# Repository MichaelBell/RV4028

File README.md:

# RV4028 - A hackable Risc-V computer

RV4028 is intended to be a modular Risc-V computer, similar to the excellent [RC2014 Z80](https://rc2014.co.uk/) homebrew computer.

The idea is to create a minimal Risc-V system that is easy to understand and extend.

The inspiration for this came from [@theJPster](https://github.com/thejpster)'s [post](https://bsky.app/profile/thejpster.org.uk/post/3m3ngtx5sfc2i).

All hardware and software are open source and permissively licensed.

## Architecture

The system bus has a 32-bit address and 16-bit data, which fits reasonably well with an RV32 system and readily available (P)SRAM chips, and runs at 3.3V.

Modules are attached by an 80-pin dual row header, similar to RC2014 modules but with 2 rows of pins instead of 1.  2mm pitch headers are used instead of 2.54mm, this makes boards slightly smaller (and cheaper), and also avoids the possibility of boards being plugged into RC2014 by mistake.

However, the pinout is chosen such that RC2014 modules might be compatible, if 3v3 capable components are used and a backplane with additional 2.54mm pitch sockets were created.  The pinout is also chosen such that modules not requiring access to the full bus can use just a single row.

## Software

The intention is to be able to run standard RV32I programs with a C SDK.  A Micropython port and Rust support are likely.

It is currently not a goal to support either real time operating systems (although this may be possible in future), or Linux (which would likely not be possible without moving to a larger FPGA).

# Initial modules

## CPU

Keeping things minimal and simple, we use a Bruno Levy's [FemtoRV](https://github.com/BrunoLevy/learn-fpga/tree/master/FemtoRV) Quark (RV32I) core with some small modifications, and a wrapper to handle breaking each 32-bit data access into 16-bit accesses.  This is the most minimal Risc-V instruction set and can fit in a small FPGA, so we use an ICE40 [HX1K](https://www.latticesemi.com/ice40), which is available in a 100-pin QFP.

A small flash is required for the FPGA configuration, a header will be provided that will allow the FPGA to be held in reset and the flash programmed.  Although it is significantly larger than required, using a 1MB [W25Q80DV](https://www.lcsc.com/datasheet/C14086.pdf) seems cost effective. 

[Schematic](cpu/cpu.pdf)

## RAM

The two candidates here are PSRAM, such as the [IS66WVE](https://www.lcsc.com/datasheet/C1350157.pdf), or SRAM such as the [CY7C1041G30](https://www.lcsc.com/datasheet/C2944680.pdf).

The PSRAM is larger but slower, and the larger capacities only seem available in BGA packages.  The linked SRAM is available in TSOP, which may allow for easier assembly.

The current RAM module uses the PSRAM.

[Schematic](ram/ram.pdf)

## ROM

Something like [SST39VF3202C](https://www.lcsc.com/datasheet/C637403.pdf) looks suitable, and available at the same access speed as the PSRAM (70ns).

ROM might not be required - we can embed a small amount of ROM (6kB) in the CPU gateware which could be enough for a simple SD card driver, allowing a program to be loaded from SD card to RAM without any ROM.

## IO

An [RP2350B](https://datasheets.raspberrypi.com/rp2350/rp2350-datasheet.pdf) is used for IO.  The board should include:
- Two UARTs
- Two I2C broken out to Qw/ST compatible ports
- A micro SD card socket
- An SPI with a couple of chip selects (this should be made easy to connect to the CPU for updating the gateware)
- Some GPIO

8 bits of address should easily be sufficient, and 8 bits of data should also be fine, which allows this to be single row.

I'm tempted to put USB on a couple of the spare backplane pins, so a single USB connection can power the system and be used to communicate with/program the RP2350.

If we also wired clock and reset from the RP2350 then it could provide a clock, meaning a separate clock module would not be required.

[Schematic](io/io.pdf) | [More details](io/README.md)

## Clock

As above, a clock module likely won't be required, but it is a nice educational addition, and would allow the machine to be used without the RP2350 based IO module.

A 14.7456MHz crystal would seem appropriate - double the clock rate of the RC2014.  Assuming IS66WVE PSRAM is used, the maximum reliable clock rate of the system should be around 17-18MHz (TBC).

An [SN74LVC1GX04](https://www.lcsc.com/datasheet/C2653063.pdf) could be used to drive the crystal.

## Backplane

USB-C socket, with data wired to spare pins for RP2350 on IO board.

AP2112K for 3.3V supply.  3v3 enable is delayed by a few milliseconds to help with power sequencing on the CPU board (the core power to the FPGA should be applied before IO voltage).

Decoupling caps, LED, reset button.  Use surface mount headers for the 2x40 pin connectors, allows all the signals to run above a nice unbroken ground plane, rather than having loads of through holes breaking up the ground planes.

# Bus timing

Addresses are always 16-bit aligned and a byte mask is used for single byte stores.

All writes complete in a two cycles.  Reads normally complete in two cycles, but wait may be asserted to extend the read cycle.

MREQ is intended to be wired to the (P)SRAM CE, so must be pulsed regularly even if reads are continuous in order to avoid exceeding max CE assertion time on PSRAM.  This is acheived by pulsing it high in the first half clock of each read cycle.  MREQ remains low at the start of a write cycle in order to support a faster clock speed when used with a IS66WVE.

IORQ is not required as the address space is sufficiently large.  It is simply set to ~A31.

LO_ADDR indicates if the address is in the bottom 16MB of the address space, to reduce the amount of address checking logic required on low addressed modules.

## Expected RAM implementation

RAM access is controlled by CE, OE, WE and byte selects.

* Address high bits are compared for the chip, CE is never asserted if the address doesn't match
* CE is MREQ
* WE is WR
* OE is RD
* Byte selects are MSK.

Writes are latched by deasserting WE and CE.  So a full store instruction that read the instruction and wrote data back to the same RAM chip would look like:

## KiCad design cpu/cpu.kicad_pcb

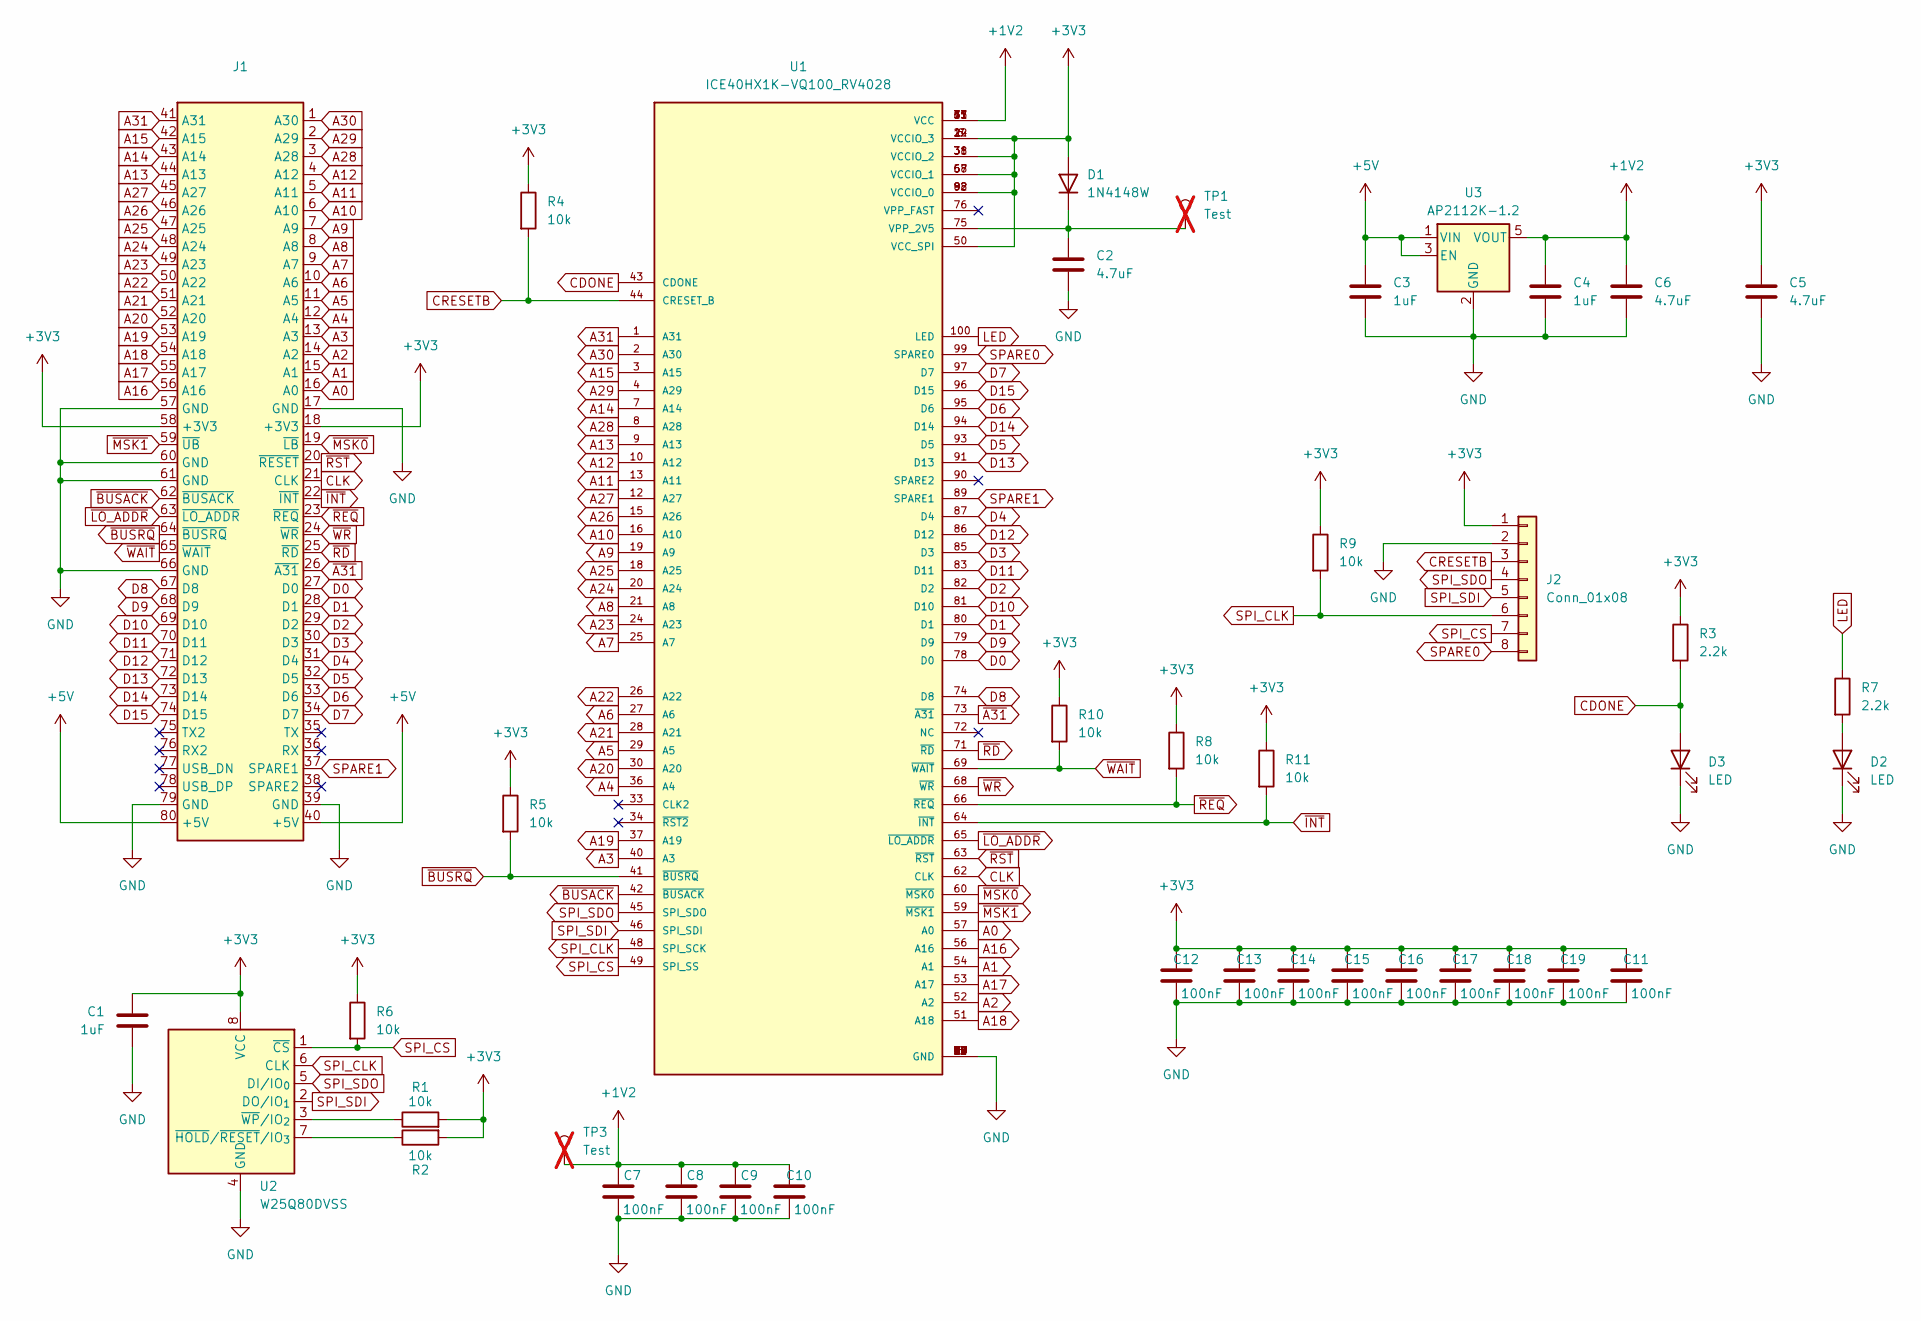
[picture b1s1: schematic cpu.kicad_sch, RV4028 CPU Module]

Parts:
C1, C3, C4: 1uF; C_0603_1608Metric; JLC C15849
C2, C5, C6: 4.7uF; C_0603_1608Metric; JLC C19666
C7, C8, C9, C10, C11, C12, C13, C14, C15, C16, C17, C18, C19: 100nF; C_0402_1005Metric; JLC C1525
D1: 1N4148W; D_SOD-123F; JLC C81598
D2: LED; LED_0603_1608Metric; JLC C2286
D3: LED; LED_0603_1608Metric; JLC C2290
J1: Module_2mm; JLC C3407
J2: Conn_01x08; PinHeader_1x08_P2.54mm_Vertical; JLC C5383116
R1, R2, R4, R5, R6, R8, R9, R10, R11: 10k; R_0402_1005Metric; JLC C25744
R3, R7: 2.2k; R_0402_1005Metric; JLC C25879
TP1, TP3: Test; TestPoint_Pad_1.5x1.5mm; not fitted
U1: ICE40HX1K-VQ100_RV4028; QFP50P1600X1600X120-100N; PARTREV 3.4; JLC C1519043
U2: W25Q80DVSS; SOIC-8_5.3x5.3mm_P1.27mm; JLC C14086
U3: AP2112K-1.2; SOT-23-5; JLC C460310

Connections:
+1V2: C4.1, C6.1, C7.2, C8.2, C9.2, C10.2, TP3.1, U1.11 (VCC), U1.35 (VCC), U1.61 (VCC), U1.77 (VCC), U3.5 (VOUT)
+3V3: C1.2, C5.1, C11.2, C12.2, C13.2, C14.2, C15.2, C16.2, C17.2, C18.2, C19.2, D1.2 (A), J1.18 (+3V3), J1.58 (+3V3), J2.1, R1.2, R2.2, R3.1, R4.1, R5.1, R6.1, R8.1, R9.1, R10.1, R11.1, U1.6 (VCCIO_3), U1.14 (VCCIO_3), U1.22 (VCCIO_3), U1.31 (VCCIO_2), U1.38 (VCCIO_2), U1.50 (VCC_SPI), U1.58 (VCCIO_1), U1.67 (VCCIO_1), U1.88 (VCCIO_0), U1.92 (VCCIO_0), U2.8 (VCC)
+5V: C3.1, J1.40 (+5V), J1.80 (+5V), U3.1 (VIN), U3.3 (EN)
A0: J1.16 (A0), U1.57 (A0)
A1: J1.15 (A1), U1.54 (A1)
A2: J1.14 (A2), U1.52 (A2)
A3: J1.13 (A3), U1.40 (A3)
A4: J1.12 (A4), U1.36 (A4)
A5: J1.11 (A5), U1.29 (A5)
A6: J1.10 (A6), U1.27 (A6)
A7: J1.9 (A7), U1.25 (A7)
A8: J1.8 (A8), U1.21 (A8)
A9: J1.7 (A9), U1.19 (A9)
A10: J1.6 (A10), U1.16 (A10)
A11: J1.5 (A11), U1.13 (A11)
A12: J1.4 (A12), U1.10 (A12)
A13: J1.44 (A13), U1.9 (A13)
A14: J1.43 (A14), U1.7 (A14)
A15: J1.42 (A15), U1.3 (A15)
A16: J1.56 (A16), U1.56 (A16)
A17: J1.55 (A17), U1.53 (A17)
A18: J1.54 (A18), U1.51 (A18)
A19: J1.53 (A19), U1.37 (A19)
A20: J1.52 (A20), U1.30 (A20)
A21: J1.51 (A21), U1.28 (A21)
A22: J1.50 (A22), U1.26 (A22)
A23: J1.49 (A23), U1.24 (A23)
A24: J1.48 (A24), U1.20 (A24)
A25: J1.47 (A25), U1.18 (A25)
A26: J1.46 (A26), U1.15 (A26)
A27: J1.45 (A27), U1.12 (A27)
A28: J1.3 (A28), U1.8 (A28)
A29: J1.2 (A29), U1.4 (A29)
A30: J1.1 (A30), U1.2 (A30)
A31: J1.41 (A31), U1.1 (A31)
CDONE: D3.2 (A), R3.2, U1.43 (CDONE)
CLK: J1.21 (CLK), U1.62 (CLK)
CRESETB: J2.3, R4.2, U1.44 (CRESET_B)
D0: J1.27 (D0), U1.78 (D0)
D1: J1.28 (D1), U1.80 (D1)
D2: J1.29 (D2), U1.82 (D2)
D3: J1.30 (D3), U1.85 (D3)
D4: J1.31 (D4), U1.87 (D4)
D5: J1.32 (D5), U1.93 (D5)
D6: J1.33 (D6), U1.95 (D6)
D7: J1.34 (D7), U1.97 (D7)
D8: J1.67 (D8), U1.74 (D8)
D9: J1.68 (D9), U1.79 (D9)
D10: J1.69 (D10), U1.81 (D10)
D11: J1.70 (D11), U1.83 (D11)
D12: J1.71 (D12), U1.86 (D12)
D13: J1.72 (D13), U1.91 (D13)
D14: J1.73 (D14), U1.94 (D14)
D15: J1.74 (D15), U1.96 (D15)
GND: C1.1, C2.2, C3.2, C4.2, C5.2, C6.2, C7.1, C8.1, C9.1, C10.1, C11.1, C12.1, C13.1, C14.1, C15.1, C16.1, C17.1, C18.1, C19.1, D2.1 (K), D3.1 (K), J1.17 (GND), J1.39 (GND), J1.57 (GND), J1.60 (GND), J1.61 (GND), J1.66 (GND), J1.79 (GND), J2.2, U1.5 (GND), U1.17 (GND), U1.23 (GND), U1.32 (GND), U1.39 (GND), U1.47 (GND), U1.55 (GND), U1.70 (GND), U1.84 (GND), U1.98 (GND), U2.4 (GND), U3.2 (GND)
LED: R7.1, U1.100 (LED)
unnamed: C2.1, D1.1 (K), TP1.1, U1.75 (VPP_2V5)
unnamed: D2.2 (A), R7.2
unnamed: R2.1, U2.7 (~HOLD/~RESET/IO_{3})
unnamed: R1.1, U2.3 (~WP/IO_{2})
SPARE0: J2.8, U1.99 (SPARE0)
SPARE1: J1.37 (SPARE1), U1.89 (SPARE1)
SPI_CLK: J2.6, R9.2, U1.48 (SPI_SCK), U2.6 (CLK)
SPI_CS: J2.7, R6.2, U1.49 (SPI_SS), U2.1 (~CS)
SPI_SDI: J2.5, U1.46 (SPI_SDI), U2.2 (DO/IO_{1})
SPI_SDO: J2.4, U1.45 (SPI_SDO), U2.5 (DI/IO_{0})
~A31: J1.26 (~A31), U1.73 (~A31)
~BUSACK: J1.62 (~BUSACK), U1.42 (~BUSACK)
~BUSRQ: J1.64 (~BUSRQ), R5.2, U1.41 (~BUSRQ)
~INT: J1.22 (~INT), R11.2, U1.64 (~INT)
~LO_ADDR: J1.63 (~LO_ADDR), U1.65 (~LO_ADDR)
~MSK0: J1.19 (~LB), U1.60 (~MSK0)
~MSK1: J1.59 (~UB), U1.59 (~MSK1)
~RD: J1.25 (~RD), U1.71 (~RD)
~REQ: J1.23 (~REQ), R8.2, U1.66 (~REQ)
~RST: J1.20 (~RESET), U1.63 (~RST)
~WAIT: J1.65 (~WAIT), R10.2, U1.69 (~WAIT)
~WR: J1.24 (~WR), U1.68 (~WR)

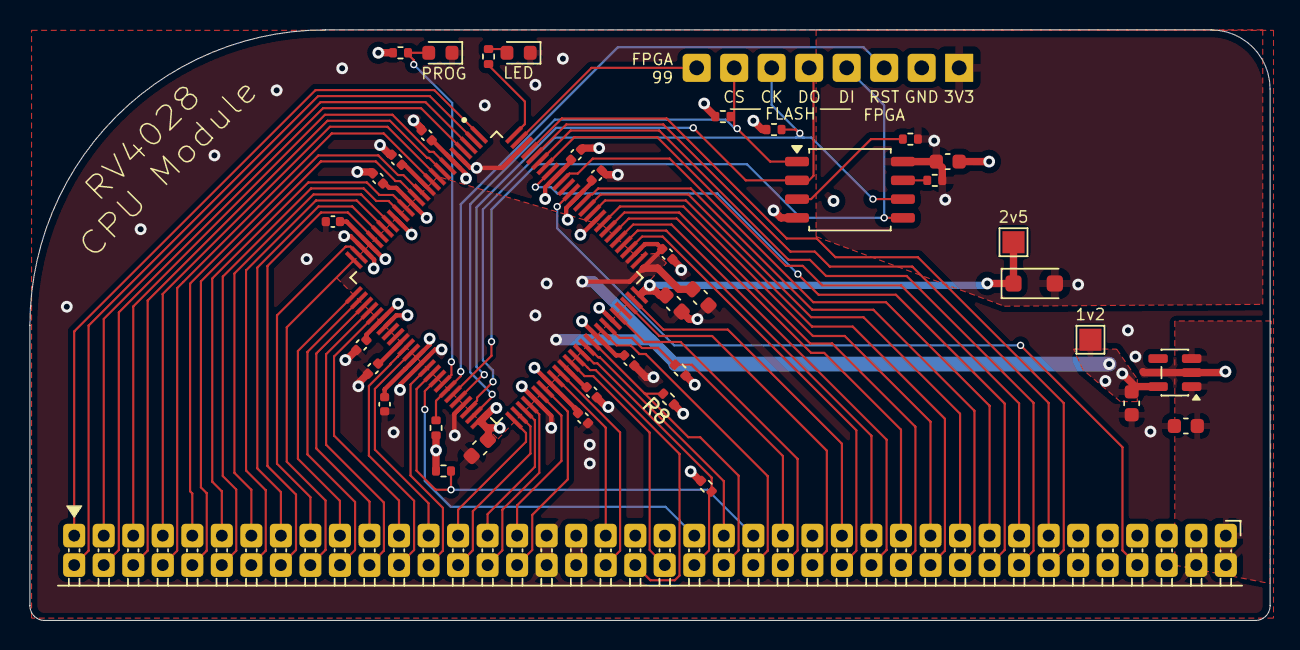
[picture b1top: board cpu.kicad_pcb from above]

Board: 4 copper layers, 84.0 x 40.0 mm, 40 parts (0 on the bottom side), 78 nets.

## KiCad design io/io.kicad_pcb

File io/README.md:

# RP2350 IO module for RV4028

## Features

Basic idea is to expose the RP2350's hardware blocks as memory mapped peripherals.

Peripherals:
- 2 UARTs (one to backplane, one on headers)
- 2 I2C (QwST connectors)
- 1 SPI with 3 or 4 chip selects (can be used for programming the FPGA)
- SD card
- Maybe a WS2812 interface (exposing 5V power)
- Further pins as general purpose IO.  Maybe could expose a PIO block?

Clock and reset are connected, and can optionally be driven, depending on the loaded firmware.

WAIT and INT should be connected.

Other wiring:
- USB to the USB pins on the backplane
- SWD to a header

## Interface

Byte at a time data - this is very suitable for UART, I2C, SPI.

Address - A1-A7 connected, plus ~A31 and A30-A28 ORed together, with the module selected when the result is low.  The modules canonical address space is therefore even addresses within 0x8FFF_FF00 - 0x8FFF_FFFF.  Accessing it at other addresses should be avoided to prevent conflicting responses from different modules (maybe we put some protection in the gateware to prevent access to invalid addresses?)

IOSEL = ~A31 OR A30 OR A29 OR A28, RDREQ = REQ OR RD and WR are needed in addition to the 7 low address pins and 8 data pins.

## Implementation

PIO programs are used to detect read and write accesses.

### Write

Watches for WR going low and then checks IOSEL, if it is high the transaction is not for this module.

If low, the address and data pins are DMA'd from the PIO into a ring buffer and an IRQ asserted to wake a CPU task to read the ring buffer.

The CPU reads while the ring buffer is not empty, and forwards the data to the peripheral based on the memory map.

PIO waits for WR to go high.

### Read

Watches for RDREQ going low and then checks IOSEL, if it is high the transaction is not for this module.

If low, the address is DMA'd to the trigger read address of a waiting DMA channel.  This reads from a table of source addresses into the read trigger address of a second waiting DMA channel, which will DMA one byte from (normally) a peripheral address to the PIO, which will set the data pins.  When RDREQ goes high the data are set back to inputs and the PIO resets.

Latency from RDREQ going low to data being presented should be around 10-15 cycles:
- Wait (2 cycles input latency)
- Jmp
- In pins (auto push)
- DMA trigger
- DMA read from lookup table
- DMA write and trigger
- DMA read from peripheral
- Out pins (auto pull)

This has a little less than 1.5 cycles to complete if WAIT isn't asserted, so is rather tight but should work if the RP2350 clock is > 12x faster than the RV4028 clock.  Could do with prototyping to check the cycle count is acheivable.

### Pin mapping

0-1 UART0 to header
2-3 Ground, so they will read as zero
4-10 A1-A7
11-18 D0-D7
19 CLK
20 RESET
21 INT
22 WAIT
23 IOSEL
24 WR
25 RD
26-27 UART1 to backplane
28-31 SPI1
32-33 I2C0
34-39 SD card (SPI0)
40-41 Additional SPI chip selects
42-43 I2C1
44 WS2812b LED data
45 LED
46-47 GPIO

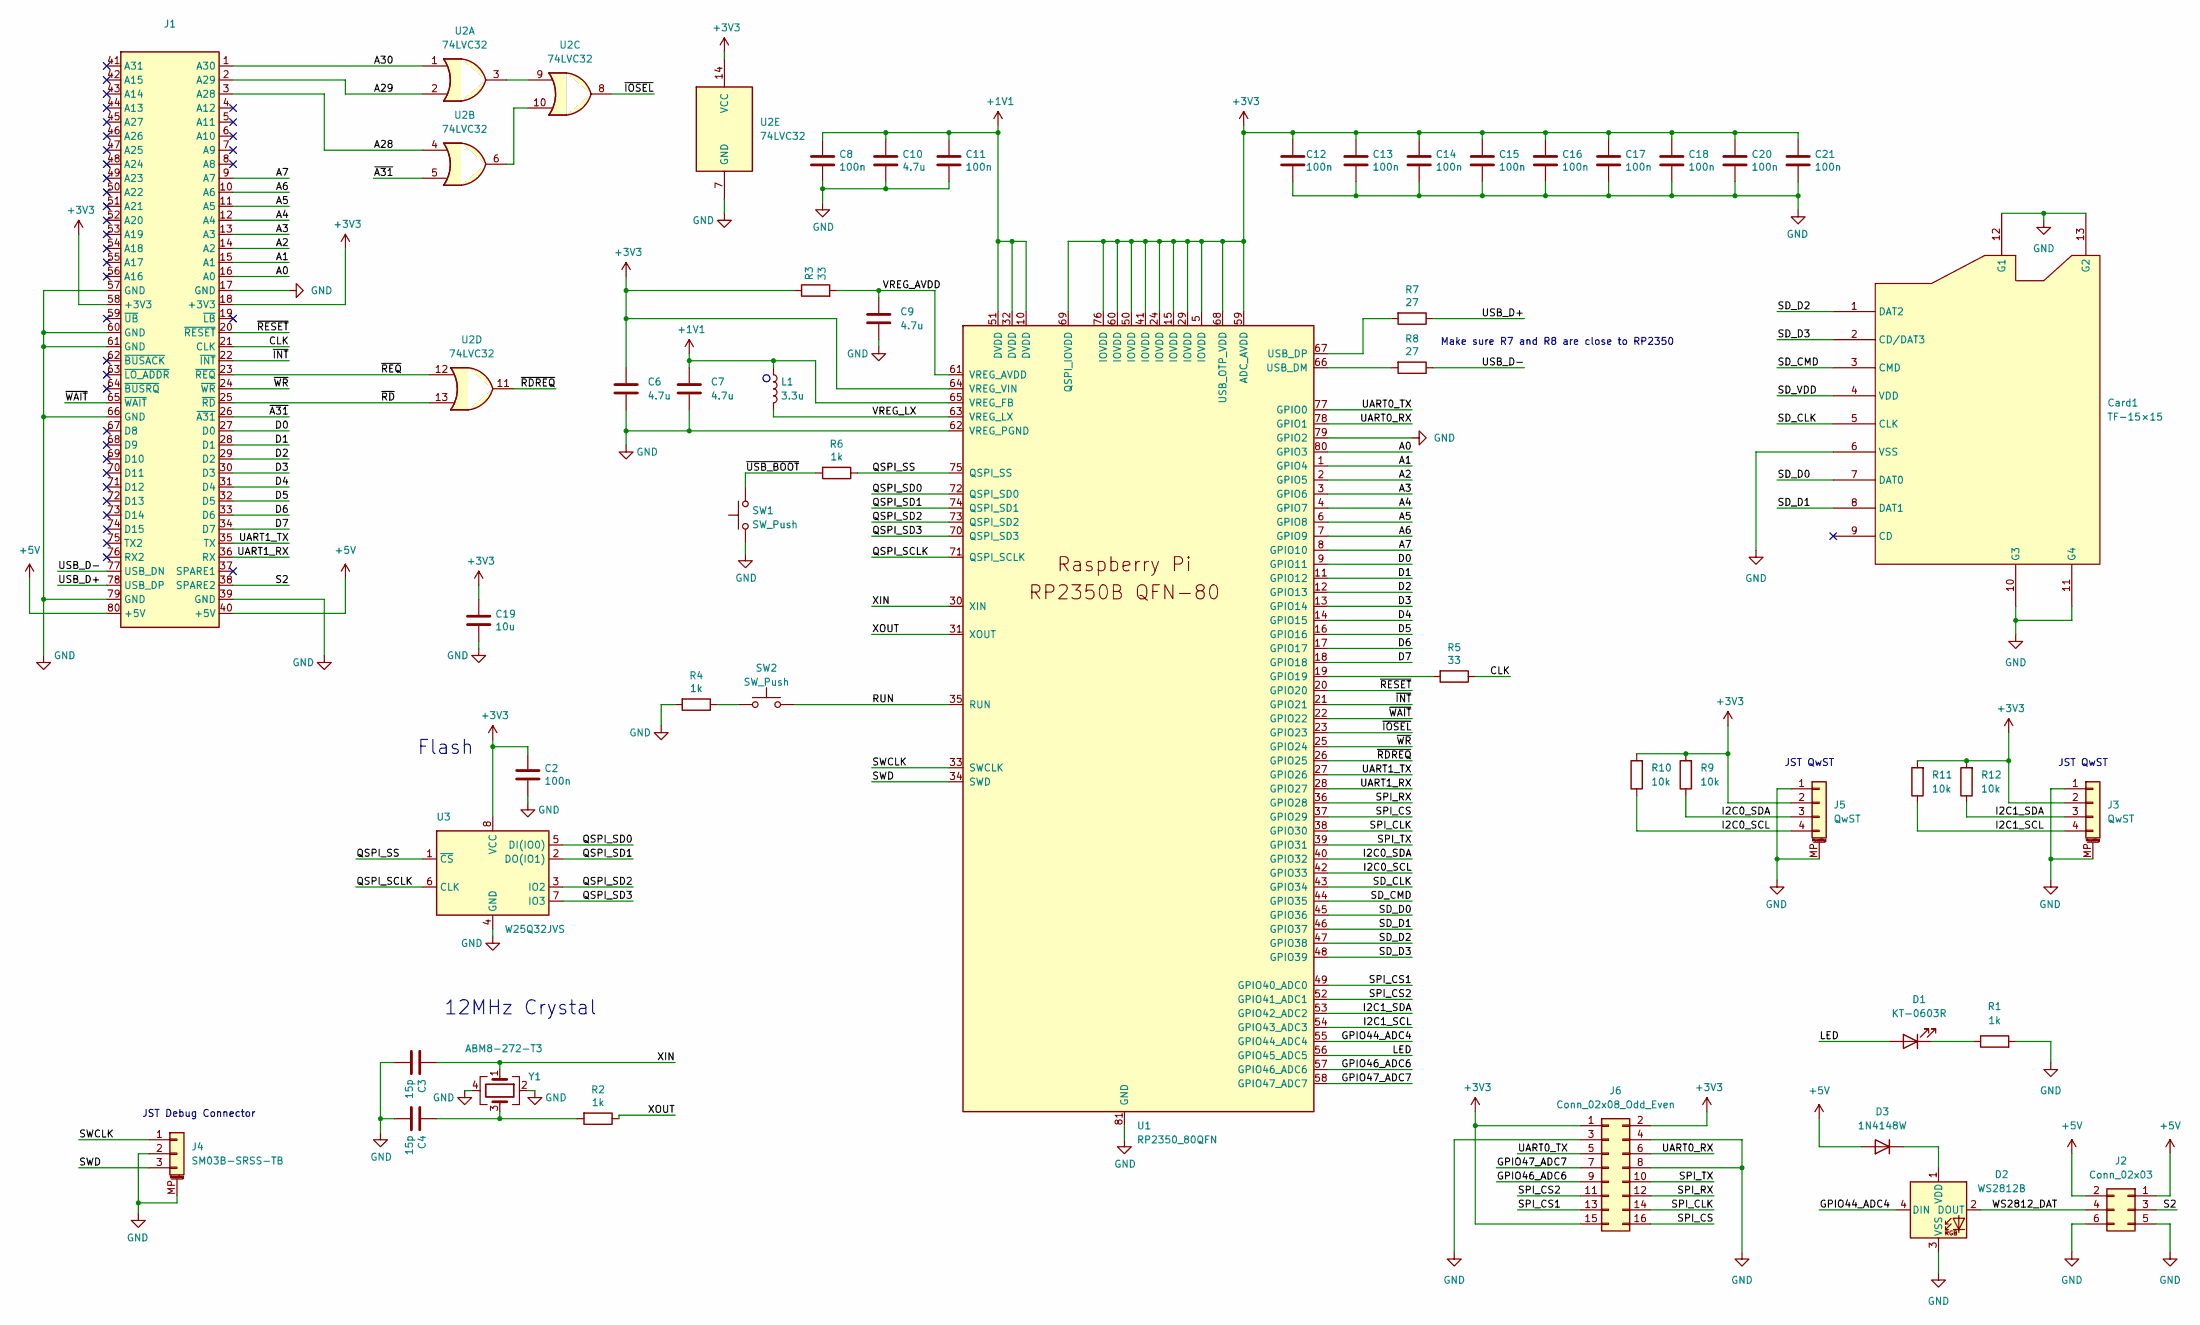
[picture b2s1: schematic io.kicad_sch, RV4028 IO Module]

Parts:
C2, C8, C11, C12, C13, C14, C15, C16, C17, C18, C20, C21: 100n; C_0402_1005Metric
C3, C4: 15p; C_0402_1005Metric
C6, C7: 4.7u; C_0402_1005Metric_small_pads
C9, C10: 4.7u; C_0402_1005Metric
C19: 10u; C_0805_2012Metric
Card1: TF-15×15; TF-SMD_TF-15-15; LCSC Part C111196
D1: KT-0603R; LED_0603_1608Metric; JLC C2286
D2: WS2812B; LED_WS2812B_PLCC4_5.0x5.0mm_P3.2mm; JLC C42417498
D3: 1N4148W; D_SOD-123F; JLC C81598
J1: Module_2mm; JLC C3407
J2: Conn_02x03; PinHeader_2x03_P2.54mm_Vertical; JLC C5383104
J3, J5: QwST; JST_SH_SM04B-SRSS-TB_1x04-1MP_P1.00mm_Horizontal; JLC C160404
J4: SM03B-SRSS-TB; JST_SH_SM03B-SRSS-TB_1x03-1MP_P1.00mm_Horizontal; JLC C160403
J6: Conn_02x08_Odd_Even; PinHeader_2x08_P2.54mm_Vertical; JLC C5383108
L1: 3.3u; L_pol_2016; JLC C42411119
R1, R2, R4, R6: 1k; R_0402_1005Metric
R3, R5: 33; R_0402_1005Metric
R7, R8: 27; R_0402_1005Metric
R9, R10, R11, R12: 10k; R_0402_1005Metric
SW1, SW2: SW_Push; SW-SMD_HX-TS-1101-C-W; JLC C36498960
U1: RP2350_80QFN; RP2350-QFN-80-1EP_10x10_P0.4mm_EP3.4x3.4mm_ThermalVias; JLC C42415655
U2: 74LVC32; SSOP-14_5.3x6.2mm_P0.65mm; JLC C2867091
U3: W25Q32JVS; SOIC-8_5.3x5.3mm_P1.27mm; JLC C179173
Y1: ABM8-272-T3; Crystal_SMD_3225-4Pin_3.2x2.5mm; JLC C20625731

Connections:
+1V1: C7.1, C8.1, C10.1, C11.1, L1.1, U1.10 (DVDD), U1.32 (DVDD), U1.51 (DVDD), U1.65 (VREG_FB)
+3V3: C2.1, C6.1, C12.1, C13.1, C14.1, C15.1, C16.1, C17.1, C18.1, C19.1, C20.1, C21.1, J1.18 (+3V3), J1.58 (+3V3), J3.2, J5.2, J6.1, J6.2, J6.15, R3.1, R9.2, R10.2, R11.2, R12.2, U1.5 (IOVDD), U1.15 (IOVDD), U1.24 (IOVDD), U1.29 (IOVDD), U1.41 (IOVDD), U1.50 (IOVDD), U1.59 (ADC_AVDD), U1.60 (IOVDD), U1.64 (VREG_VIN), U1.68 (USB_OTP_VDD), U1.69 (QSPI_IOVDD), U1.76 (IOVDD), U2.14 (VCC), U3.8 (VCC)
+5V: D3.2 (A), J1.40 (+5V), J1.80 (+5V), J2.1, J2.2
/A0: J1.16 (A0), U1.80 (GPIO3)
/A1: J1.15 (A1), U1.1 (GPIO4)
/A2: J1.14 (A2), U1.2 (GPIO5)
/A3: J1.13 (A3), U1.3 (GPIO6)
/A4: J1.12 (A4), U1.4 (GPIO7)
/A5: J1.11 (A5), U1.6 (GPIO8)
/A6: J1.10 (A6), U1.7 (GPIO9)
/A7: J1.9 (A7), U1.8 (GPIO10)
/A28: J1.3 (A28), U2.4
/A29: J1.2 (A29), U2.2
/A30: J1.1 (A30), U2.1
/CLK: J1.21 (CLK), R5.1
/D0: J1.27 (D0), U1.9 (GPIO11)
/D1: J1.28 (D1), U1.11 (GPIO12)
/D2: J1.29 (D2), U1.12 (GPIO13)
/D3: J1.30 (D3), U1.13 (GPIO14)
/D4: J1.31 (D4), U1.14 (GPIO15)
/D5: J1.32 (D5), U1.16 (GPIO16)
/D6: J1.33 (D6), U1.17 (GPIO17)
/D7: J1.34 (D7), U1.18 (GPIO18)
/GPIO44_ADC4: D2.4 (DIN), U1.55 (GPIO44_ADC4)
/GPIO46_ADC6: J6.9, U1.57 (GPIO46_ADC6)
/GPIO47_ADC7: J6.7, U1.58 (GPIO47_ADC7)
/I2C0_SCL: J5.4, R10.1, U1.42 (GPIO33)
/I2C0_SDA: J5.3, R9.1, U1.40 (GPIO32)
/I2C1_SCL: J3.4, R11.1, U1.54 (GPIO43_ADC3)
/I2C1_SDA: J3.3, R12.1, U1.53 (GPIO42_ADC2)
/LED: D1.2 (A), U1.56 (GPIO45_ADC5)
/QSPI_SCLK: U1.71 (QSPI_SCLK), U3.6 (CLK)
/QSPI_SD0: U1.72 (QSPI_SD0), U3.5 (DI(IO0))
/QSPI_SD1: U1.74 (QSPI_SD1), U3.2 (DO(IO1))
/QSPI_SD2: U1.73 (QSPI_SD2), U3.3 (IO2)
/QSPI_SD3: U1.70 (QSPI_SD3), U3.7 (IO3)
/QSPI_SS: R6.1, U1.75 (QSPI_SS), U3.1 (~CS)
/RUN: SW2.2, U1.35 (RUN)
/S2: J1.38 (SPARE2), J2.3
/SD_CLK: Card1.5 (CLK), U1.43 (GPIO34)
/SD_CMD: Card1.3 (CMD), U1.44 (GPIO35)
/SD_D0: Card1.7 (DAT0), U1.45 (GPIO36)
/SD_D1: Card1.8 (DAT1), U1.46 (GPIO37)
/SD_D2: Card1.1 (DAT2), U1.47 (GPIO38)
/SD_D3: Card1.2 (CD/DAT3), U1.48 (GPIO39)
/SD_VDD: Card1.4 (VDD)
/SPI_CLK: J6.14, U1.38 (GPIO30)
/SPI_CS: J6.16, U1.37 (GPIO29)
/SPI_CS1: J6.13, U1.49 (GPIO40_ADC0)
/SPI_CS2: J6.11, U1.52 (GPIO41_ADC1)
/SPI_RX: J6.12, U1.36 (GPIO28)
/SPI_TX: J6.10, U1.39 (GPIO31)
/SWCLK: J4.1, U1.33 (SWCLK)
/SWD: J4.3, U1.34 (SWD)
/UART0_RX: J6.6, U1.78 (GPIO1)
/UART0_TX: J6.5, U1.77 (GPIO0)
/UART1_RX: J1.36 (RX), U1.28 (GPIO27)
/UART1_TX: J1.35 (TX), U1.27 (GPIO26)
/USB_D+: J1.78 (USB_DP), R7.1
/USB_D-: J1.77 (USB_DN), R8.1
/VREG_AVDD: C9.1, R3.2, U1.61 (VREG_AVDD)
/VREG_LX: L1.2, U1.63 (VREG_LX)
/WS2812_DAT: D2.2 (DOUT), J2.4
/XIN: C3.1, U1.30 (XIN), Y1.1
/XOUT: R2.1, U1.31 (XOUT)
/~A31: J1.26 (~A31), U2.5
/~INT: J1.22 (~INT), U1.21 (GPIO21)
/~IOSEL: U1.23 (GPIO23), U2.8
/~RDREQ: U1.26 (GPIO25), U2.11
/~RD: J1.25 (~RD), U2.13
/~REQ: J1.23 (~REQ), U2.12
/~RESET: J1.20 (~RESET), U1.20 (GPIO20)
/~USB_BOOT: R6.2, SW1.2
/~WAIT: J1.65 (~WAIT), U1.22 (GPIO22)
/~WR: J1.24 (~WR), U1.25 (GPIO24)
GND: C2.2, C3.2, C4.2, C6.2, C7.2, C8.2, C9.2, C10.2, C11.2, C12.2, C13.2, C14.2, C15.2, C16.2, C17.2, C18.2, C19.2, C20.2, C21.2, Card1.6 (VSS), Card1.10 (G3), Card1.11 (G4), Card1.12 (G1), Card1.13 (G2), D2.3 (VSS), J1.17 (GND), J1.39 (GND), J1.57 (GND), J1.60 (GND), J1.61 (GND), J1.66 (GND), J1.79 (GND), J2.5, J2.6, J3.1, J3.MP (MountPin), J4.2, J4.MP (MountPin), J5.1, J5.MP (MountPin), J6.3, J6.4, J6.8, R1.2, R4.2, SW1.1, U1.62 (VREG_PGND), U1.79 (GPIO2), U1.81 (GND), U2.7 (GND), U3.4 (GND), Y1.2, Y1.4
unnamed: C4.1, R2.2, Y1.3
unnamed: D1.1 (K), R1.1
unnamed: D2.1 (VDD), D3.1 (K)
unnamed: R4.1, SW2.1
unnamed: R5.2, U1.19 (GPIO19)
unnamed: R8.2, U1.66 (USB_DM)
unnamed: R7.2, U1.67 (USB_DP)
unnamed: U2.3, U2.9
unnamed: U2.6, U2.10

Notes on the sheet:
JST Debug Connector
JST QwST
Make sure R7 and R8 are close to RP2350
Flash
12MHz Crystal

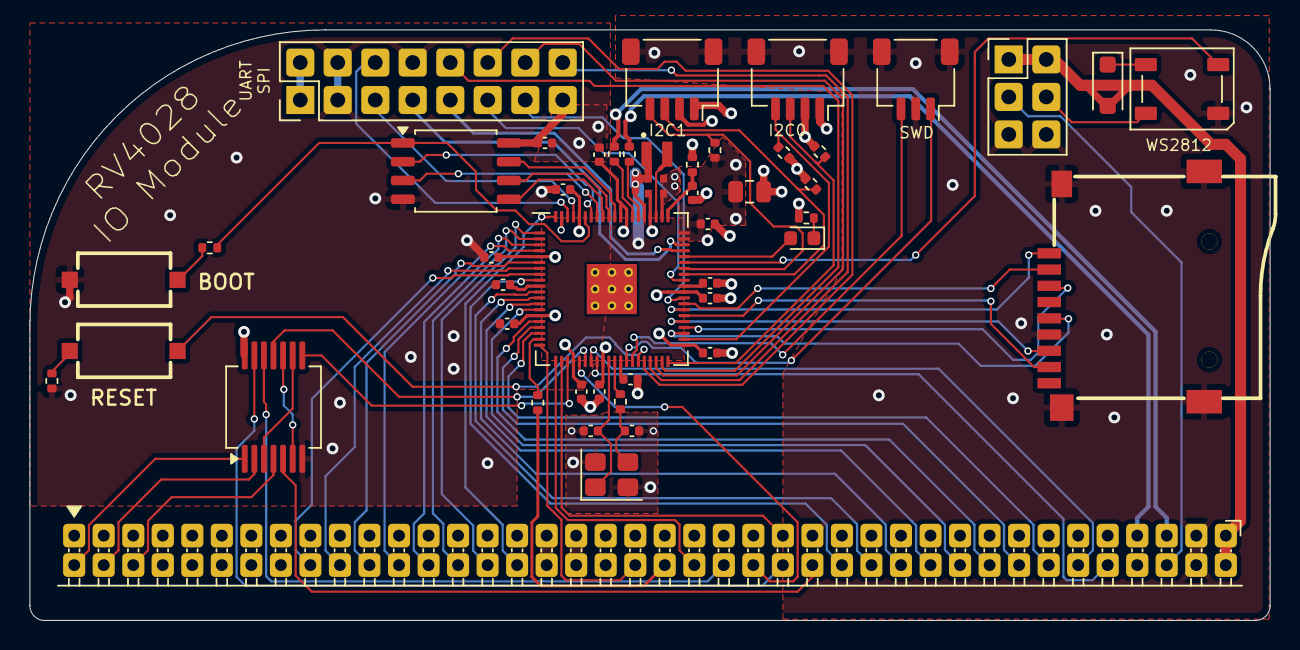
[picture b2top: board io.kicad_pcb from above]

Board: 4 copper layers, 84.0 x 40.0 mm, 48 parts (0 on the bottom side), 84 nets.

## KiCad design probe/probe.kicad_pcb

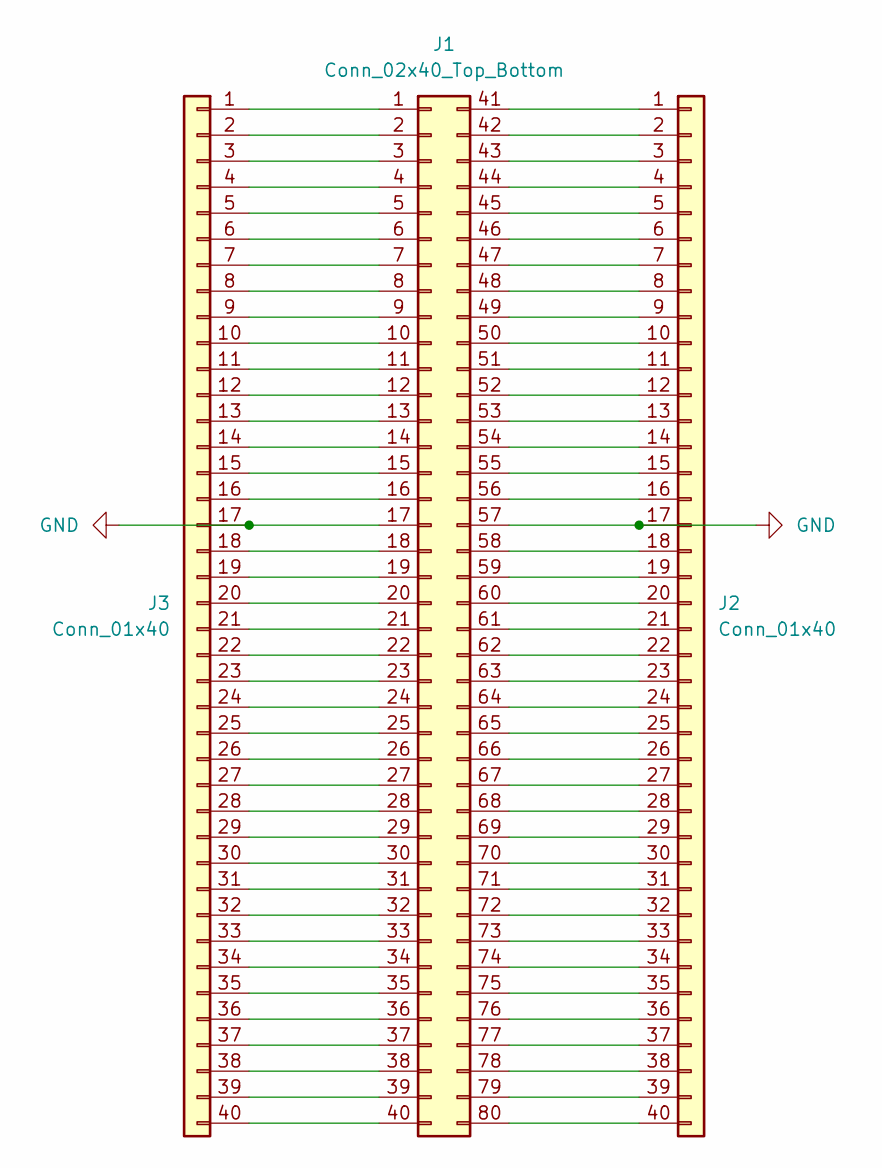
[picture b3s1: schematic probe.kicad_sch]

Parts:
J1: Conn_02x40_Top_Bottom; PinSocket_2x40_P2.00mm_Vertical
J2, J3: Conn_01x40; PinHeader_1x40_P2.00mm_Vertical

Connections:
GND: J1.17, J1.57, J2.17, J3.17
unnamed: J1.1, J3.1
unnamed: J1.2, J3.2
unnamed: J1.3, J3.3
unnamed: J1.4, J3.4
unnamed: J1.5, J3.5
unnamed: J1.6, J3.6
unnamed: J1.7, J3.7
unnamed: J1.8, J3.8
unnamed: J1.9, J3.9
unnamed: J1.10, J3.10
unnamed: J1.11, J3.11
unnamed: J1.12, J3.12
unnamed: J1.13, J3.13
unnamed: J1.14, J3.14
unnamed: J1.15, J3.15
unnamed: J1.16, J3.16
unnamed: J1.18, J3.18
unnamed: J1.19, J3.19
unnamed: J1.20, J3.20
unnamed: J1.21, J3.21
unnamed: J1.22, J3.22
unnamed: J1.23, J3.23
unnamed: J1.24, J3.24
unnamed: J1.25, J3.25
unnamed: J1.26, J3.26
unnamed: J1.27, J3.27
unnamed: J1.28, J3.28
unnamed: J1.29, J3.29
unnamed: J1.30, J3.30
unnamed: J1.31, J3.31
unnamed: J1.32, J3.32
unnamed: J1.33, J3.33
unnamed: J1.34, J3.34
unnamed: J1.35, J3.35
unnamed: J1.36, J3.36
unnamed: J1.37, J3.37
unnamed: J1.38, J3.38
unnamed: J1.39, J3.39
unnamed: J1.40, J3.40
unnamed: J1.41, J2.1
unnamed: J1.42, J2.2
unnamed: J1.43, J2.3
unnamed: J1.44, J2.4
unnamed: J1.45, J2.5
unnamed: J1.46, J2.6
unnamed: J1.47, J2.7
unnamed: J1.48, J2.8
unnamed: J1.49, J2.9
unnamed: J1.50, J2.10
unnamed: J1.51, J2.11
unnamed: J1.52, J2.12
unnamed: J1.53, J2.13
unnamed: J1.54, J2.14
unnamed: J1.55, J2.15
unnamed: J1.56, J2.16
unnamed: J1.58, J2.18
unnamed: J1.59, J2.19
unnamed: J1.60, J2.20
unnamed: J1.61, J2.21
unnamed: J1.62, J2.22
unnamed: J1.63, J2.23
unnamed: J1.64, J2.24
unnamed: J1.65, J2.25
unnamed: J1.66, J2.26
unnamed: J1.67, J2.27
unnamed: J1.68, J2.28
unnamed: J1.69, J2.29
unnamed: J1.70, J2.30
unnamed: J1.71, J2.31
unnamed: J1.72, J2.32
unnamed: J1.73, J2.33
unnamed: J1.74, J2.34
unnamed: J1.75, J2.35
unnamed: J1.76, J2.36
unnamed: J1.77, J2.37
unnamed: J1.78, J2.38
unnamed: J1.79, J2.39
unnamed: J1.80, J2.40

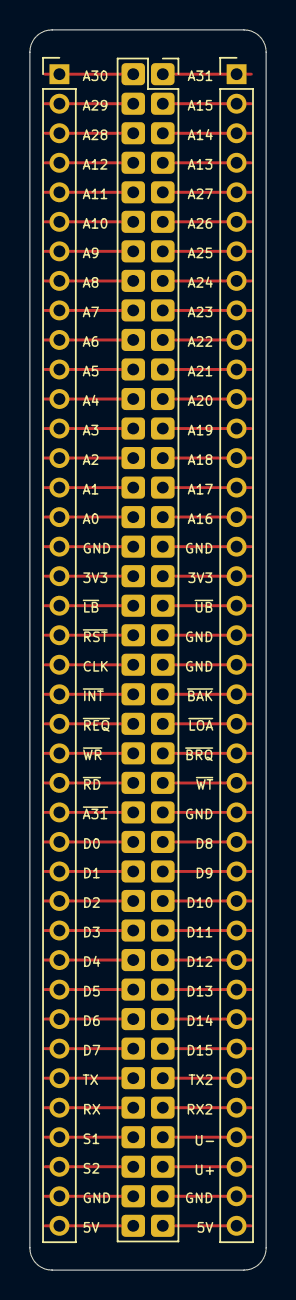
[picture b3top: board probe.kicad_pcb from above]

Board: 2 copper layers, 16.0 x 84.0 mm, 3 parts (0 on the bottom side), 79 nets.

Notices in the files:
backplane/backplane.kicad_pcb:
© Michael Bell 2026
